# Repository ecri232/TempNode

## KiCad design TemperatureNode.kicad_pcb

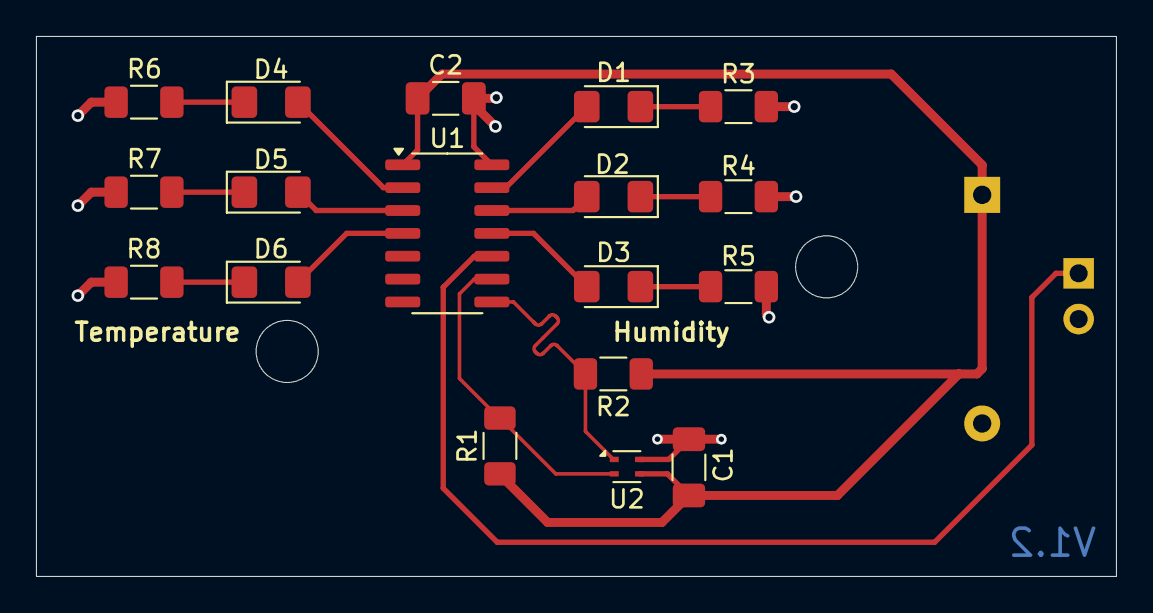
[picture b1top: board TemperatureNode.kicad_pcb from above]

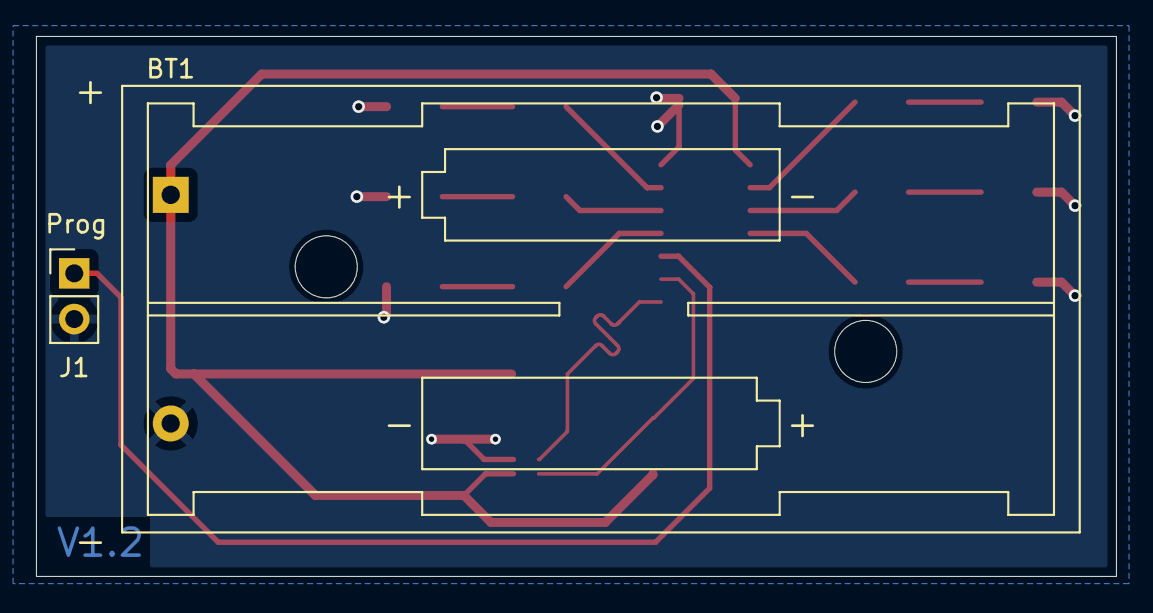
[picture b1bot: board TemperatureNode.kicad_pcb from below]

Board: 2 copper layers, 60.0 x 30.0 mm, 20 parts (2 on the bottom side), 17 nets.

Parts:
BT1: Battery; BatteryHolder_Keystone_2468_2xAAA
C1, C2: 100nF; C_1206_3216Metric_Pad1.33x1.80mm_HandSolder
D1, D2, D3, D4, D5, D6: LED; LED_1206_3216Metric_Pad1.42x1.75mm_HandSolder
J1: Conn_01x02_Pin; PinHeader_1x02_P2.54mm_Vertical
R1, R2: 10k; R_1206_3216Metric_Pad1.30x1.75mm_HandSolder
R3, R4, R6, R7: 60.4; R_1206_3216Metric_Pad1.30x1.75mm_HandSolder
R5, R8: 300; R_1206_3216Metric_Pad1.30x1.75mm_HandSolder
U1: ATtiny414-SS; SOIC-14_3.9x8.7mm_P1.27mm
U2: SHT40-AD1B-R3; Sensirion_DFN-4_1.5x1.5mm_P0.8mm_SHT4x_NoCentralPad

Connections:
+3.3V: BT1.1 (+), C1.1, C2.1, R1.1, R2.1, U1.1 (VCC), U2.3 (VDD)
/UPDI: J1.1, U1.10 (~RESET/PA0)
GND: BT1.2 (-), C1.2, C2.2, J1.2, R3.2, R4.2, R5.2, R6.2, R7.2, R8.2, U1.14 (GND), U2.4 (VSS)
unnamed: D1.2 (A), U1.13 (PA3)
unnamed: D1.1 (K), R3.1
unnamed: D2.2 (A), U1.12 (PA2)
unnamed: D2.1 (K), R4.1
unnamed: D3.2 (A), U1.11 (PA1)
unnamed: D3.1 (K), R5.1
unnamed: D4.2 (A), U1.2 (PA4)
unnamed: D4.1 (K), R6.1
unnamed: D5.2 (A), U1.3 (PA5)
unnamed: D5.1 (K), R7.1
unnamed: D6.2 (A), U1.4 (PA6)
unnamed: D6.1 (K), R8.1
unnamed: R1.2, U1.9 (PB0), U2.2 (SCL)
unnamed: R2.2, U1.8 (PB1), U2.1 (SDA)

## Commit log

2024-03-04 Intial commit, v1
2024-03-08 Changed I2C routing to match length and eliminate via
2024-03-09 Added calculations file and updated I2C routing for more clearance

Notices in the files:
TemperatureNode.kicad_pcb:
creativecommons.org/licenses/by/4.0
License: CC BY 4.0
